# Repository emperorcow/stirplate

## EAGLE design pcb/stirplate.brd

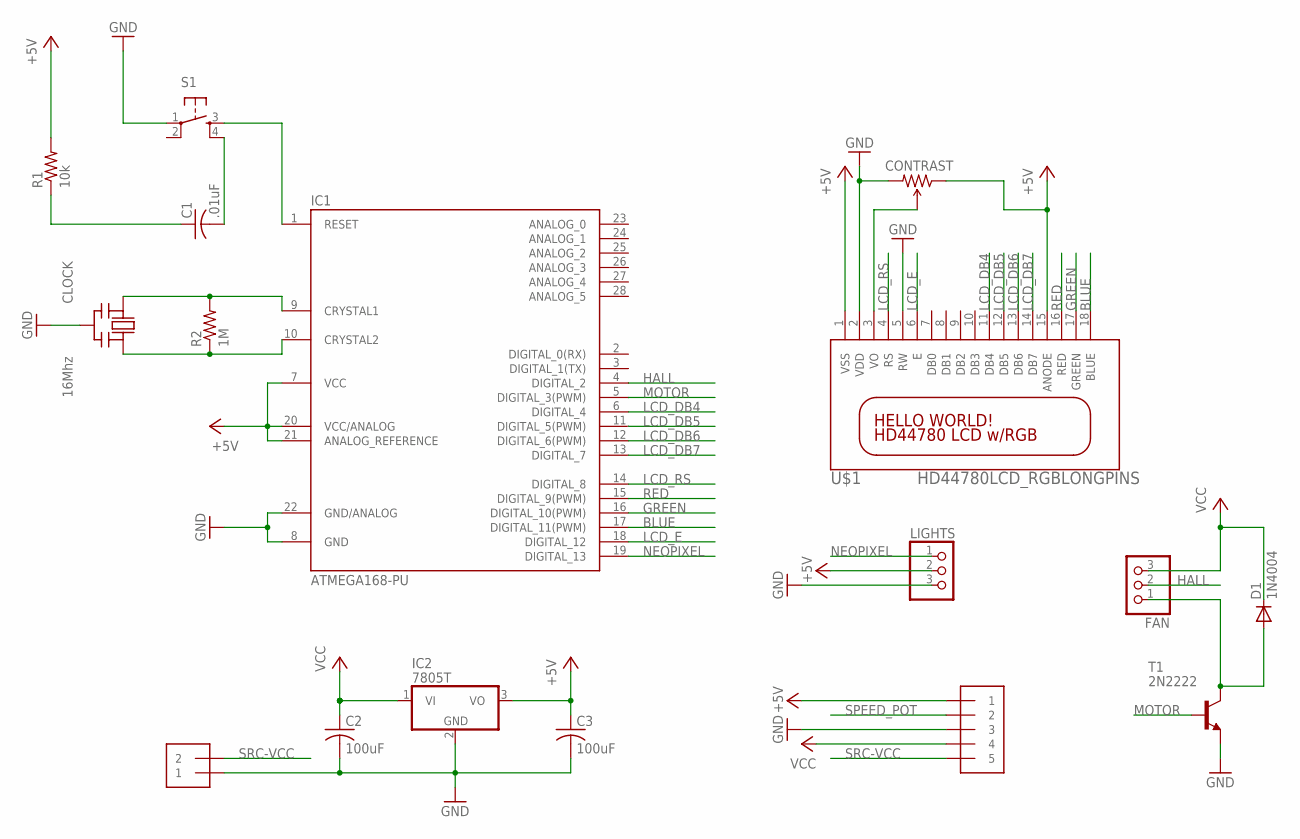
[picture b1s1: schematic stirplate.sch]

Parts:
C1: .01uF; C025-030X050
C2, C3: 100uF; C025-030X050
CLOCK: 16Mhz; CERM_OSC
CONTRAST: TRIMPOTPTH; TRIM_POT_PTH
D1: 1N4004; DO41-10
FAN: PINHD-1X3CB; 1X03-CLEANBIG
IC1: ATMEGA168-PU; DIL28-3
IC2: 7805T; TO220H
LIGHTS: PINHD-1X3; 1X03
POWER: 1X2-3.5MM
R1: 10k; 0204/7
R2: 1M; 0204/7
S1: TAC_SWITCHPTH; TACTILE-PTH
SPEED: 1X5; 1X05-3.5MM
T1: 2N2222; TO92-EBC-OVAL
U$1: HD44780LCD_RGBLONGPINS; LCD1602-RGB

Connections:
+5V: C3.1, CONTRAST.1 (CCW), IC1.7 (VCC), IC1.20 (VCC/ANALOG), IC1.21 (ANALOG_REFERENCE), IC2.3 (VO), LIGHTS.2, R1.2, SPEED.1, U$1.15 (ANODE)
BLUE: IC1.17 (DIGITAL_11(PWM)), U$1.18 (BLUE)
GND: C2.2, C3.2, CLOCK.P$2 (GND), IC1.8 (GND), IC1.22 (GND/ANALOG), IC2.2 (GND), LIGHTS.3, POWER.1, S1.1, SPEED.3, T1.E, U$1.5 (RW)
GREEN: IC1.16 (DIGITAL_10(PWM)), U$1.17 (GREEN)
HALL: FAN.2, IC1.4 (DIGITAL_2)
LCD_DB4: IC1.6 (DIGITAL_4), U$1.11 (DB4)
LCD_DB5: IC1.11 (DIGITAL_5(PWM)), U$1.12 (DB5)
LCD_DB6: IC1.12 (DIGITAL_6(PWM)), U$1.13 (DB6)
LCD_DB7: IC1.13 (DIGITAL_7), U$1.14 (DB7)
LCD_E: IC1.18 (DIGITAL_12), U$1.6 (E)
LCD_RS: IC1.14 (DIGITAL_8), U$1.4 (RS)
MOTOR: IC1.5 (DIGITAL_3(PWM)), T1.B
unnamed: CLOCK.P$1 (IN), IC1.9 (CRYSTAL1), R2.2
unnamed: CLOCK.P$3 (OUT), IC1.10 (CRYSTAL2), R2.1
unnamed: C1.2, S1.4
unnamed: IC1.1 (RESET), S1.3
unnamed: C1.1, R1.1
unnamed: D1.A, FAN.1, T1.C
unnamed: CONTRAST.2 (WIPER), U$1.3 (VO)
NEOPIXEL: IC1.19 (DIGITAL_13), LIGHTS.1
RED: IC1.15 (DIGITAL_9(PWM)), U$1.16 (RED)
SPEED_POT: SPEED.2
SRC-VCC: POWER.2, SPEED.5
VCC: C2.1, D1.C, FAN.3, IC2.1 (VI), SPEED.4
VDD: CONTRAST.3 (CW), U$1.2 (VDD)
VSS: U$1.1 (VSS)

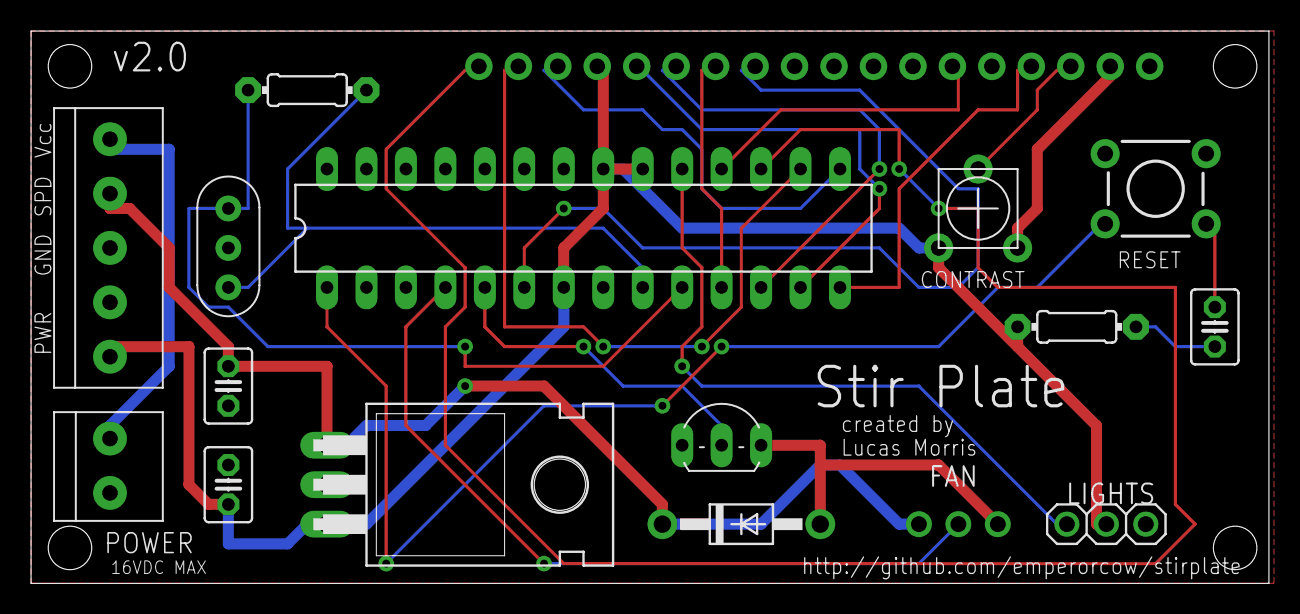
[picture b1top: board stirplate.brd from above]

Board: 2 copper layers, 79.7 x 35.5 mm, 17 parts (1 on the bottom side), 24 nets.

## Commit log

2013-12-10 some changes starting on a new smaller board design
2014-04-10 Moved 2.0 schematic to Eagle
2014-04-11 Finished Eagle conversion, mostly finished board
2014-05-08 Fixed a few issues on the new eagle board
    Upgraded LCD to an Adafruit RGB, fixed some routing caused by that.
    Moved header for radial pot to a 1x5 screw terminal and fixed routing on
    that.

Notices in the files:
parts and their libraries:
SparkFun-Electromechanical: Licensing: Creative Commons ShareAlike 4.0 International - https://creativecommons.org/licenses/by-sa/4.0
